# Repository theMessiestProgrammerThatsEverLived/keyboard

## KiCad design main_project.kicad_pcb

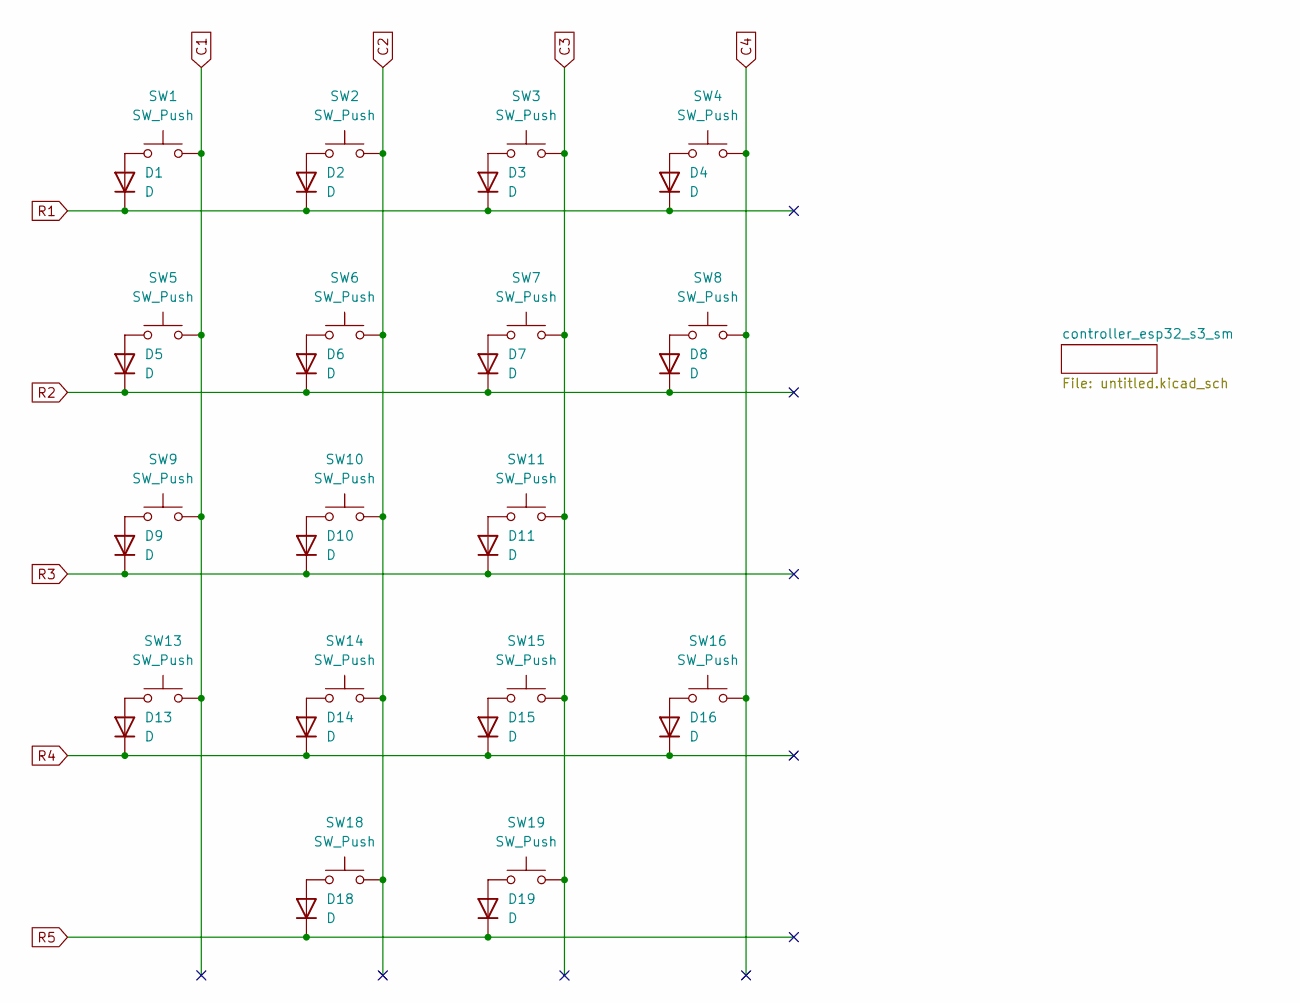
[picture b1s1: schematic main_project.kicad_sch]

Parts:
D1, D2, D3, D4, D5, D6, D7, D8, D9, D10, D11, D13, D14, D15, D16, D18, D19: D; D_A-405_P7.62mm_Horizontal
SW1, SW2, SW3, SW4, SW5, SW6, SW7: SW_Push; SW_Hotswap_Kailh_MX
SW8, SW16: SW_Push; SW_Hotswap_Kailh_MX_2.00u_90deg
SW9, SW10, SW11, SW13, SW14, SW15, SW19: SW_Push; SW_Hotswap_Kailh_MX_1.00u
SW18: SW_Push; SW_Hotswap_Kailh_MX_2.00u

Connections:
C1: SW1.2, SW5.2, SW9.2, SW13.2; also elsewhere on the board
C2: SW2.2, SW6.2, SW10.2, SW14.2, SW18.2; also elsewhere on the board
C3: SW3.2, SW7.2, SW11.2, SW15.2, SW19.2; also elsewhere on the board
C4: SW4.2, SW8.2, SW16.2; also elsewhere on the board
unnamed: D1.2 (A), SW1.1
unnamed: D2.2 (A), SW2.1
unnamed: D3.2 (A), SW3.1
unnamed: D4.2 (A), SW4.1
unnamed: D5.2 (A), SW5.1
unnamed: D6.2 (A), SW6.1
unnamed: D7.2 (A), SW7.1
unnamed: D8.2 (A), SW8.1
unnamed: D9.2 (A), SW9.1
unnamed: D10.2 (A), SW10.1
unnamed: D11.2 (A), SW11.1
unnamed: D13.2 (A), SW13.1
unnamed: D14.2 (A), SW14.1
unnamed: D15.2 (A), SW15.1
unnamed: D16.2 (A), SW16.1
unnamed: D18.2 (A), SW18.1
unnamed: D19.2 (A), SW19.1
R1: D1.1 (K), D2.1 (K), D3.1 (K), D4.1 (K); also elsewhere on the board
R2: D5.1 (K), D6.1 (K), D7.1 (K), D8.1 (K); also elsewhere on the board
R3: D9.1 (K), D10.1 (K), D11.1 (K); also elsewhere on the board
R4: D13.1 (K), D14.1 (K), D15.1 (K), D16.1 (K); also elsewhere on the board
R5: D18.1 (K), D19.1 (K); also elsewhere on the board

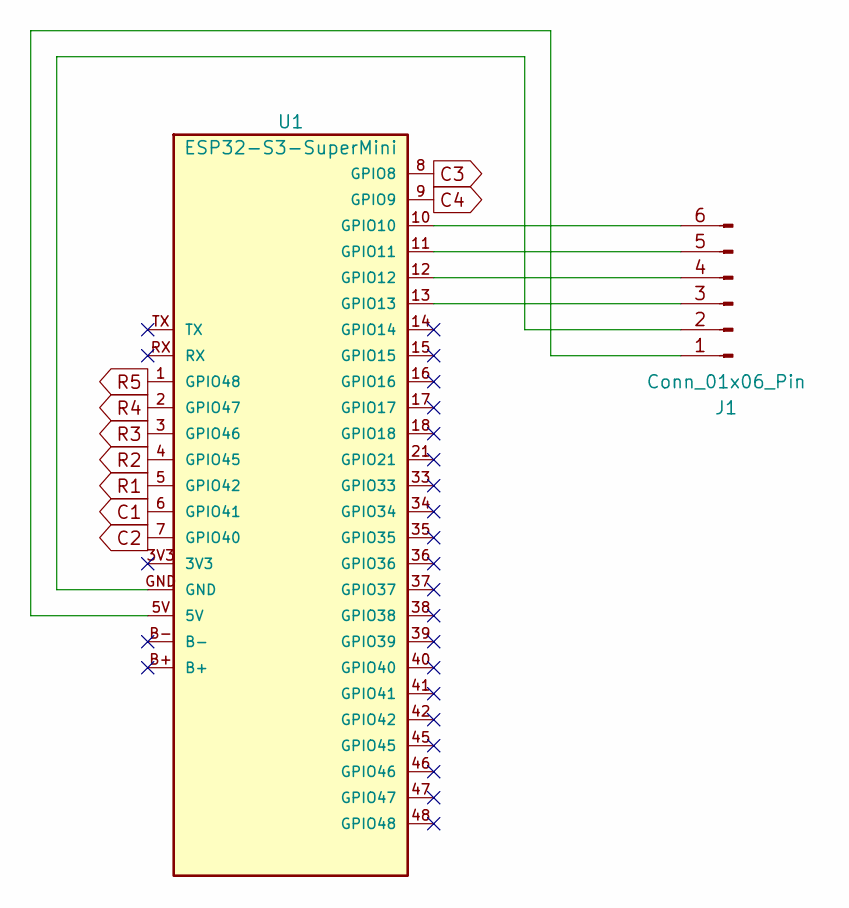
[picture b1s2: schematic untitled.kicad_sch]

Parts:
J1: Conn_01x06_Pin; PinHeader_1x06_P2.54mm_Vertical
U1: ESP32-S3-SuperMini

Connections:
C1: U1.6 (GPIO41); also elsewhere on the board
C2: U1.7 (GPIO40); also elsewhere on the board
C3: U1.8 (GPIO8); also elsewhere on the board
C4: U1.9 (GPIO9); also elsewhere on the board
unnamed: J1.1, U1.5V
unnamed: J1.2, U1.GND
unnamed: J1.3, U1.13 (GPIO13)
unnamed: J1.4, U1.12 (GPIO12)
unnamed: J1.5, U1.11 (GPIO11)
unnamed: J1.6, U1.10 (GPIO10)
R1: U1.5 (GPIO42); also elsewhere on the board
R2: U1.4 (GPIO45); also elsewhere on the board
R3: U1.3 (GPIO46); also elsewhere on the board
R4: U1.2 (GPIO47); also elsewhere on the board
R5: U1.1 (GPIO48); also elsewhere on the board

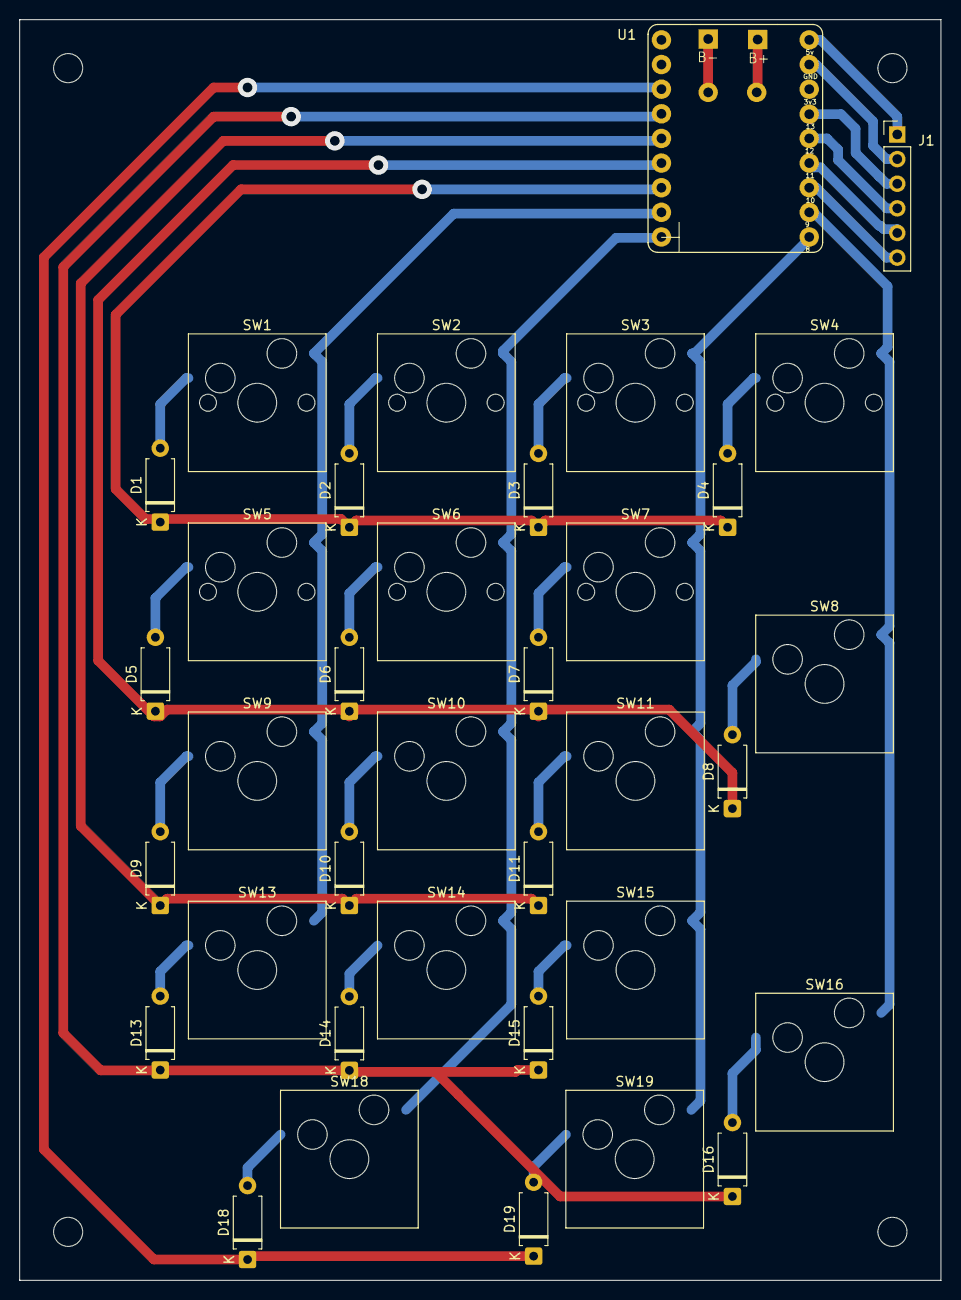
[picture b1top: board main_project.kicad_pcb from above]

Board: 2 copper layers, 95.0 x 130.0 mm, 36 parts (0 on the bottom side), 32 nets.
